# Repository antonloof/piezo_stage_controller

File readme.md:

a piezeo controller

if I finish it that is ...
outputs 0-10V on 6 outputs to drive 2x MDT693B (thorlabs)

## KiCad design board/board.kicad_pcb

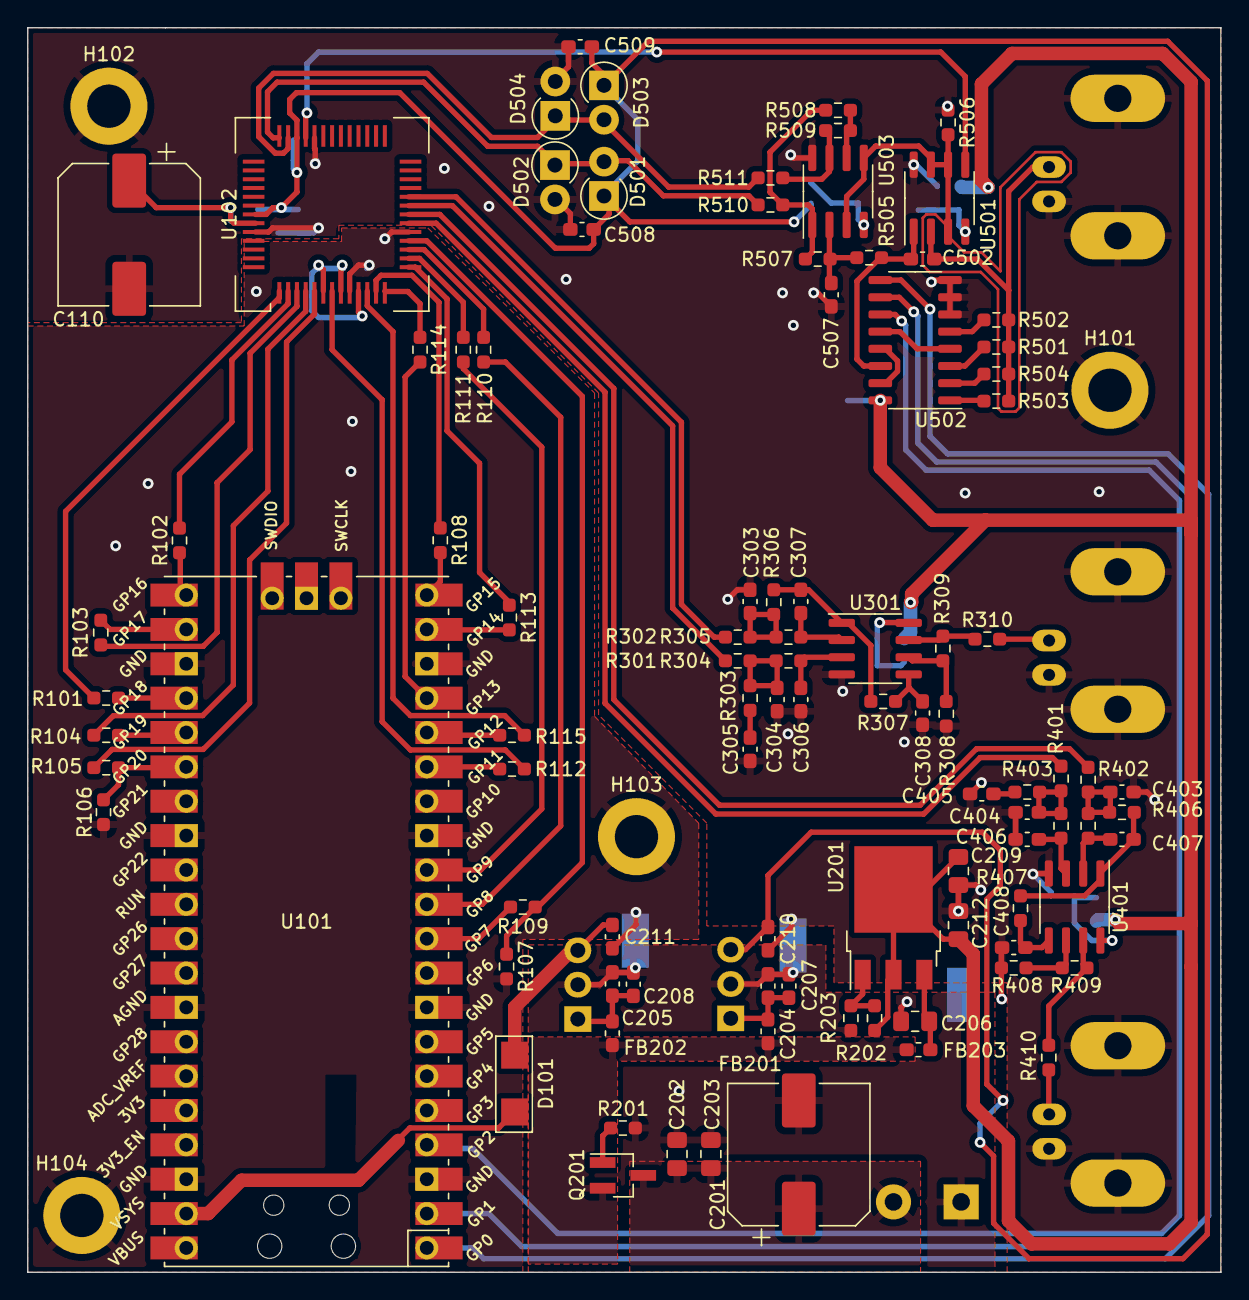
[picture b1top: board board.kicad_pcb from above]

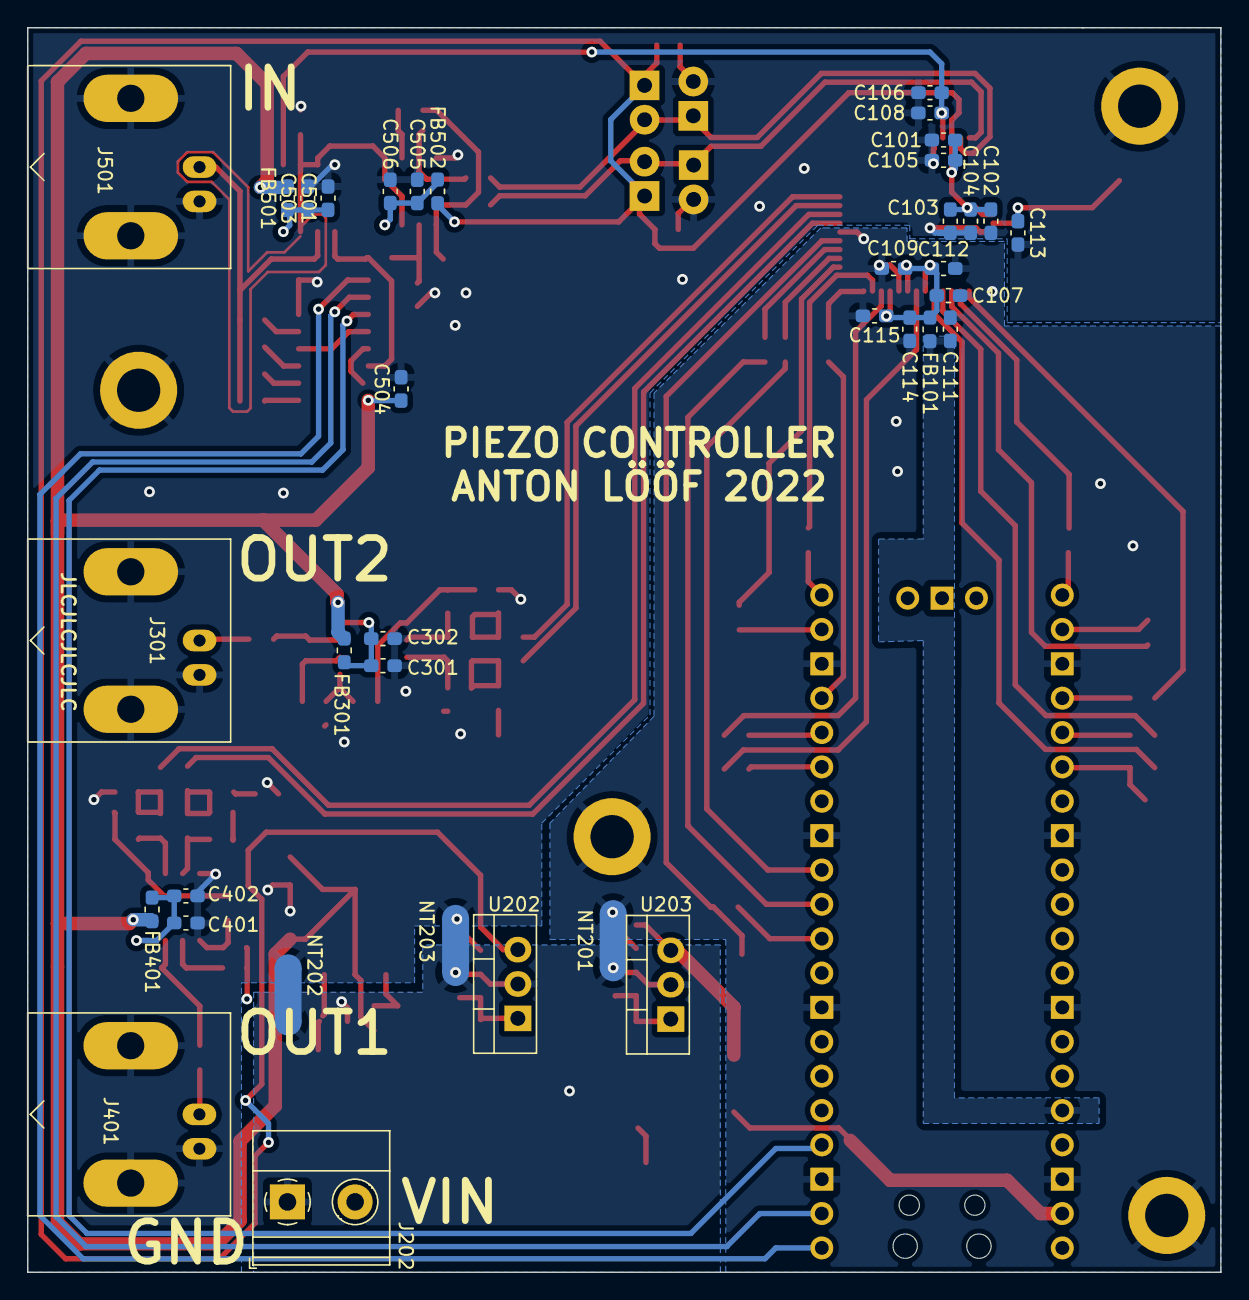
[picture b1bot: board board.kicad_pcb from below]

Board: 2 copper layers, 88.2 x 92.0 mm, 136 parts (37 on the bottom side), 90 nets.

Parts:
C101, C107, C301, C401, C501, C505: 22u; C_0603_1608Metric_Pad1.08x0.95mm_HandSolder
C102, C103, C108, C109, C111, C112, C113, C114, C115, C204, C205, C207, C208, C210, C211, C302, C402, C503, C504, C506, C508, C509: 100n; C_0603_1608Metric_Pad1.08x0.95mm_HandSolder
C104, C105: 10n; C_0603_1608Metric_Pad1.08x0.95mm_HandSolder
C106: 4u7; C_0603_1608Metric_Pad1.08x0.95mm_HandSolder
C110, C201: 330u; CP_Elec_10x10
C202, C203, C206, C209, C212: 10u 16V; C_0805_2012Metric_Pad1.18x1.45mm_HandSolder
C303, C403: 1n8; C_0603_1608Metric_Pad1.08x0.95mm_HandSolder
C304, C404: 5n6; C_0603_1608Metric_Pad1.08x0.95mm_HandSolder
C305, C405: 22u DNM; C_0603_1608Metric_Pad1.08x0.95mm_HandSolder
C306, C406: 1n2; C_0603_1608Metric_Pad1.08x0.95mm_HandSolder
C307, C407: 390p; C_0603_1608Metric_Pad1.08x0.95mm_HandSolder
C308, C408: 100p; C_0603_1608Metric_Pad1.08x0.95mm_HandSolder
C502, C507: 10p; C_0603_1608Metric_Pad1.08x0.95mm_HandSolder
D101: RSX301L-30TE25; SOD-106
D501, D502, D503, D504: 3v9; D_DO-41_SOD81_P2.54mm_Vertical_AnodeUp
FB101, FB201, FB202, FB203, FB301, FB401, FB501, FB502: BLM18AG102SN1D; L_0603_1608Metric_Pad1.05x0.95mm_HandSolder
H101, H102, H103, H104: MountingHole_Pad; MountingHole_3.2mm_M3_ISO7380_Pad
J202: Conn_01x02; TerminalBlock_Phoenix_MKDS-1,5-2_1x02_P5.00mm_Horizontal
J301, J401, J501: Conn_Coaxial; BNC_Amphenol_B6252HB-NPP3G-50_Horizontal
NT201, NT202, NT203: NetTie_2; NetTie-2_SMD_Pad2.0mm
Q201: CPH3350; SOT-23_Handsoldering
R101, R102, R103, R104, R105, R108, R109, R110, R111, R112, R113, R114, R115, R310, R410, R510, R511: 33; R_0603_1608Metric_Pad0.98x0.95mm_HandSolder
R106, R107, R201, R307, R308, R407, R408, R503, R505, R506, R507, R508, R509: 10k; R_0603_1608Metric_Pad0.98x0.95mm_HandSolder
R202: 100; R_0603_1608Metric_Pad0.98x0.95mm_HandSolder
R203: 750; R_0603_1608Metric_Pad0.98x0.95mm_HandSolder
R301, R401: 1k65; R_0603_1608Metric_Pad0.98x0.95mm_HandSolder
R302, R402: 5k49; R_0603_1608Metric_Pad0.98x0.95mm_HandSolder
R303, R403: 1k87; R_0603_1608Metric_Pad0.98x0.95mm_HandSolder
R304, R404: 887; R_0603_1608Metric_Pad0.98x0.95mm_HandSolder
R305, R405: 2k94; R_0603_1608Metric_Pad0.98x0.95mm_HandSolder
R306, R406: 4k75; R_0603_1608Metric_Pad0.98x0.95mm_HandSolder
R309, R409: 21k; R_0603_1608Metric_Pad0.98x0.95mm_HandSolder
R501: 1M; R_0603_1608Metric_Pad0.98x0.95mm_HandSolder
R502: 100k; R_0603_1608Metric_Pad0.98x0.95mm_HandSolder
R504: 1k; R_0603_1608Metric_Pad0.98x0.95mm_HandSolder
U101: Pico; RPi_Pico_SMD_TH
U102: CS42438; QFP-52_14x14_Pitch0.65mm
U201: AZ1117-ADJ; TO-252-3_TabPin2
U202, U203: L7805; TO-220-3_Vertical
U301, U401, U501, U503: lmc6042; SOIC-8_3.9x4.9mm_P1.27mm
U502: HEF4053B; SO-16_3.9x9.9mm_P1.27mm

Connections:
+3V3: C107.1, C109.1, C112.1, C114.1, C115.1, FB101.2, U102.6 (Vlc), U102.8 (Vdd), U102.10 (Vls)
+5VA: C101.1, C102.1, C103.1, C104.1, C105.1, C210.1, C508.1, C509.1, D501.1 (K), D503.1 (K), FB502.2, U102.37 (Va), U102.46 (Va), U202.3 (OUT)
+5VD: C211.1, D101.2 (A), U203.3 (OUT)
/AIN_N: D501.2 (A), D502.1 (K), R510.2, U102.39 (AIN_1_P)
/AIN_P: D503.2 (A), D504.1 (K), R511.2, U102.38 (AIN_1_N)
/a_input/VBIAS: C106.1, C108.1, U102.36 (Vq), U501.5 (+)
/a_input/photo_in: C502.1, J501.1 (In), R501.1, R502.1, R503.1, R504.1, U501.2 (-)
/a_input/single_2_diff_fb: R508.1, R509.1, U503.6 (-)
/a_input/transz_filtered: C507.2, R505.2, R507.1, U503.2 (-)
/a_input/transz_out: C502.2, R505.1, U501.1, U502.14 (1Z)
/a_input/transz_x1: U502.4 (3Z), U502.12 (1Y0)
/a_input/transz_x2: U502.13 (1Y1), U502.15 (2Z)
/a_input/vbias_buf: R506.2, U501.3 (+), U501.6 (-), U501.7, U503.3 (+), U503.5 (+)
/a_input/vdda_filt_single_to_diff: C505.1, C506.1, FB502.1, U503.4 (V-)
/a_input/vdda_filt_tranz: C501.1, C503.1, FB501.1, U501.4 (V-)
/a_input/vout_n_prer: R507.2, R508.2, R510.1, U503.1
/a_input/vout_p_prer: R509.2, R511.1, U503.7
/dac_aux_lrck: R111.2, U101.12 (GPIO9)
/dac_aux_lrck_term: R111.1, U102.15 (AUX_LRCK)
/dac_aux_sclk: R110.2, U101.11 (GPIO8)
/dac_aux_sclk_term: R110.1, U102.16 (AUX_SCLK)
/dac_aux_sdin: R109.2, U101.10 (GPIO7)
/dac_aux_sdin_term: R107.1, R109.1, U102.17 (AUX_SDIN)
/dac_ctrl_cipo: R102.1, U101.21 (GPIO16)
/dac_ctrl_cipo_term: R102.2, U102.2 (SDA/CDOUT)
/dac_ctrl_clk: R101.1, U101.24 (GPIO18)
/dac_ctrl_clk_term: R101.2, U102.1 (SCL/CCLK)
/dac_ctrl_copi: R104.1, U101.25 (GPIO19)
/dac_ctrl_copi_term: R104.2, U102.4 (AD1/CDIN)
/dac_ctrl_csn: R103.1, U101.22 (GPIO17)
/dac_ctrl_csn_term: R103.2, U102.3 (AD0/CSn)
/dac_ctrl_rstn: R105.1, R106.1, U101.26 (GPIO20)
/dac_ctrl_rstn_term: R105.2, U102.5 (RSTn)
/dac_fs: R112.2, U101.15 (GPIO11)
/dac_fs_term: R112.1, U102.7 (FS)
/dac_mclk: R108.2, U101.20 (GPIO15)
/dac_mclk_term: R108.1, U102.12 (MCLK)
/dac_sclk: R115.2, U101.16 (GPIO12)
/dac_sclk_term: R115.1, U102.11 (SCLK)
/dac_sdin: R113.2, U101.19 (GPIO14)
/dac_sdin_term: R113.1, U102.14 (DAC_SDIN)
/dac_sdout: R114.2, U101.17 (GPIO13)
/dac_sdout_term: R114.1, U102.13 (ADC_SDOUT)
/out_1_N: R401.1, U102.19 (AOUT_1_N)
/out_1_P: R402.1, U102.20 (AOUT_1_P)
/out_2_N: R302.1, U102.22 (AOUT_2_N)
/out_2_P: R301.1, U102.21 (AOUT_2_P)
/output_stage1/ctrl_output: J401.1 (In), R410.2
/output_stage1/ctrl_output_pre_prot: R409.2, R410.1, U401.7
/output_stage1/dac_filt_n: C407.2, R405.2, U401.2 (-)
/output_stage1/dac_filt_out: C407.1, R406.2, R407.1, U401.1
/output_stage1/dac_filt_p: C406.2, R404.2, U401.3 (+)
/output_stage1/dac_filt_sum_n: C403.1, R402.2, R405.1, R406.1
/output_stage1/dac_filt_sum_p: C404.2, R401.2, R403.1, R404.1
/output_stage1/gain_in: C408.1, R407.2, U401.5 (+)
/output_stage1/gain_inv: R408.2, R409.1, U401.6 (-)
/output_stage1/vdda_filt: C401.1, C402.1, FB401.1, U401.8 (V+)
/output_stage/ctrl_output: J301.1 (In), R310.2
/output_stage/ctrl_output_pre_prot: R309.2, R310.1, U301.7
/output_stage/dac_filt_n: C307.2, R305.2, U301.2 (-)
/output_stage/dac_filt_out: C307.1, R306.2, R307.1, U301.1
/output_stage/dac_filt_p: C306.2, R304.2, U301.3 (+)
/output_stage/dac_filt_sum_n: C303.1, R302.2, R305.1, R306.1
/output_stage/dac_filt_sum_p: C304.2, R301.2, R303.1, R304.1
/output_stage/gain_in: C308.1, R307.2, U301.5 (+)
/output_stage/gain_inv: R308.2, R309.1, U301.6 (-)
/output_stage/vdda_filt: C301.1, C302.1, FB301.1, U301.8 (V+)
/pico_3v3_out: C111.1, FB101.1, U101.36 (3V3)
/pico_vin: D101.1 (K), U101.39 (VSYS)
/power/5va_in: C204.1, C207.1, FB201.2, U202.1 (IN)
/power/5vd_in: C205.1, C208.1, FB202.2, U203.1 (IN)
/power/va_in: C206.1, FB203.2, U201.3 (VI)
/power/vin: C201.1, C202.1, C203.1, J202.2, Q201.3 (D)
/power/vprot: FB201.1, FB202.1, FB203.1, Q201.2 (S)
/transz_rf1: U101.4 (GPIO2), U502.11 (S1)
/transz_rf2: U101.2 (GPIO1), U502.10 (S2)
/transz_rf3: U101.1 (GPIO0), U502.9 (S3)
/vfilt: C110.1, C113.1, U102.47 (FILT+)
GNDA: C101.2, C102.2, C103.2, C104.2, C105.2, C106.2, C108.2, C110.2, C113.2, C209.2, C210.2, C212.2, C301.2, C302.2, C303.2, C304.1, C305.1, C306.1, C308.2, C401.2, C402.2, C403.2, C404.1, C405.1, C406.1, C408.2, C501.2, C503.2, C504.2, C505.2, C506.2, C507.1, C508.2, C509.2, D502.2 (A), D504.2 (A), H101.1, H102.1, J301.2 (Ext), J401.2 (Ext), J501.2 (Ext), NT202.2, NT203.2, R308.1, R408.1, R506.1, U102.35 (AGND), U102.48 (AGND), U301.4 (V-), U401.4 (V-), U501.8 (V+), U502.6 (E_n), U502.7 (VEE), U502.8 (VSS), U503.8 (V+)
GNDD: C107.2, C109.2, C111.2, C112.2, C114.2, C115.2, C211.2, H103.1, H104.1, NT201.1, R106.2, R107.2, U101.3 (GND), U101.8 (GND), U101.13 (GND), U101.18 (GND), U101.23 (GND), U101.28 (GND), U101.33 (AGND), U101.38 (GND), U102.9 (DGND), U102.18 (DGND)
GNDPWR: C201.2, C202.2, C203.2, C204.2, C205.2, C206.2, C207.2, C208.2, J202.1, NT201.2, NT202.1, NT203.1, R201.2, R203.2, U202.2 (GND), U203.2 (GND)
unnamed: C305.2, R303.2
unnamed: C405.2, R403.2
unnamed: Q201.1 (G), R201.1
unnamed: R202.2, R203.1, U201.1 (ADJ)
unnamed: R501.2, U502.3 (3Y1)
unnamed: R502.2, U502.5 (3Y0)
unnamed: R503.2, U502.1 (2Y1)
unnamed: R504.2, U502.2 (2Y0)
VDDA: C209.1, C212.1, C504.1, FB301.2, FB401.2, FB501.2, R202.1, U201.2 (VO), U502.16 (VDD)

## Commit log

2022-02-08 Add kicad lib and readme
2022-02-08 Schema with power section and start of cpu dac interface
2022-02-09 add sw to try to figure out clocking
2022-02-10 schema for test of dac done
    start layout
2022-02-11 some layout
2022-02-12 Some more layout, digital side has been reorganized
    looking into single to diff conversion. with the biases
2022-02-13 some simerino
2022-02-15 Finalize input tranz amp, to diff, protection
    layout left
2022-02-21 some pcb digital moved
2022-02-26 do the gng
2022-02-26 pcb done
    attempt at doing some sw. builds but not tested
2022-02-27 Try fab board but fail. verify sw
2022-02-27 Order pcb
2022-02-28 rm some files
2022-04-02 add proper footprint for codec
2022-04-02 stuff
